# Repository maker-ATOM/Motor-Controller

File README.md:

# Motor-Controller

For firmware refer codes directory, this directory contains only PCB files

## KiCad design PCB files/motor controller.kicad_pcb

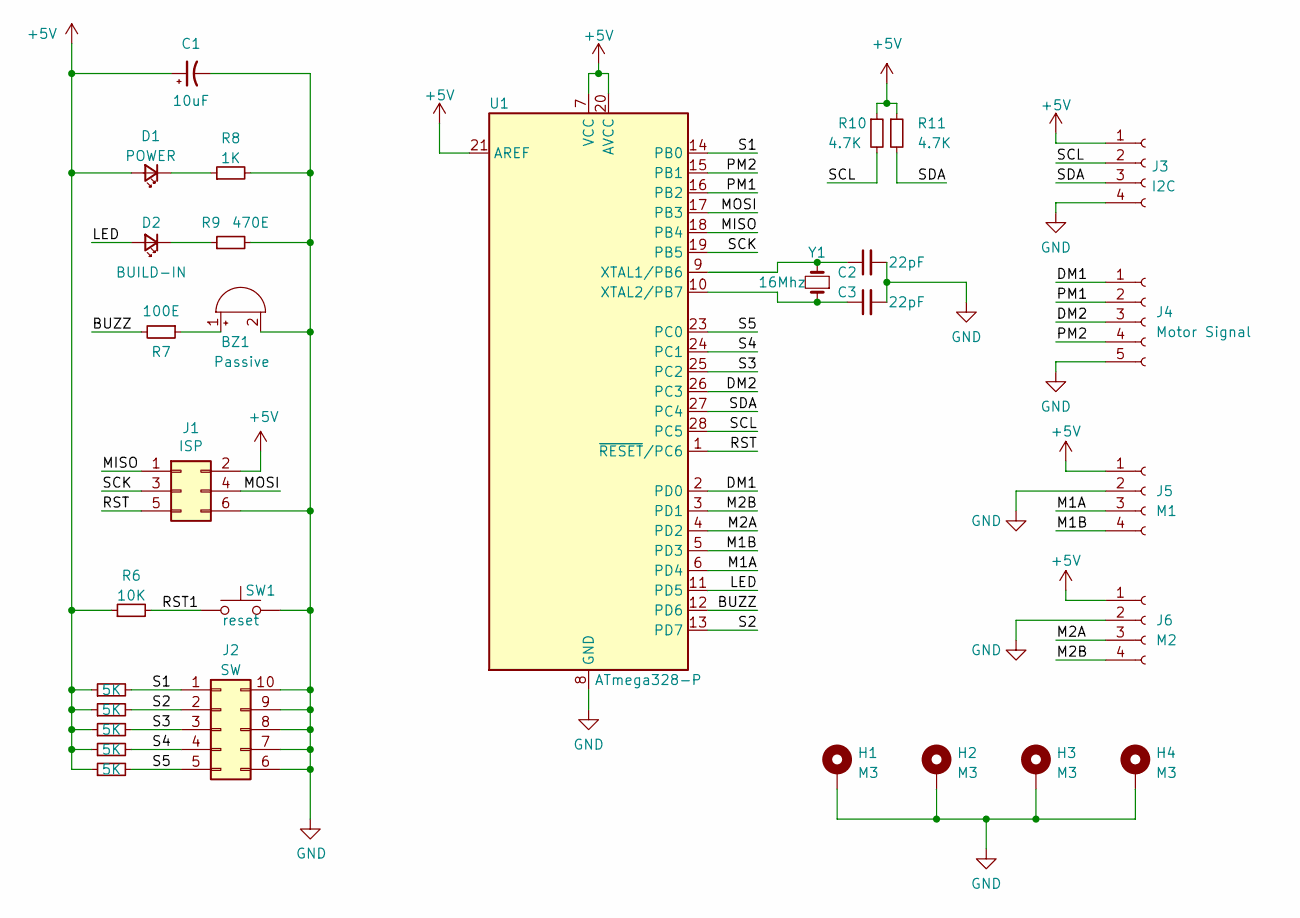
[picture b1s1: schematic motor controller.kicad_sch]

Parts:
BZ1: Passive; MagneticBuzzer_ProSignal_ABT-410-RC
C1: 10uF; CP_Elec_4x3.9
C2, C3: 22pF; C_0805_2012Metric
D1: POWER; LED_0805_2012Metric
D2: BUILD-IN; LED_0805_2012Metric
H1, H2, H3, H4: M3; MountingHole_3.2mm_M3_DIN965_Pad
J1: ISP; PinSocket_2x03_P2.54mm_Vertical
J2: SW; SW_DIP_SPSTx05_Slide_9.78x14.88mm_W7.62mm_P2.54mm
J3: I2C; JST_EH_S4B-EH_1x04_P2.50mm_Horizontal
J4: Motor Signal; PinSocket_1x05_P2.54mm_Vertical
J5: M1; JST_EH_S4B-EH_1x04_P2.50mm_Horizontal
J6: M2; JST_EH_S4B-EH_1x04_P2.50mm_Horizontal
R1, R2, R3, R4, R5: 5K; R_0805_2012Metric
R6: 10K; R_0805_2012Metric
R7: 100E; R_0805_2012Metric
R8: 1K; R_0805_2012Metric
R9: 470E; R_0805_2012Metric
R10, R11: 4.7K; R_0805_2012Metric
SW1: reset; SW_PUSH_6mm
U1: ATmega328-P; DIP-28_W7.62mm
Y1: 16Mhz; Crystal_SMD_HC49-SD

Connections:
+5V: C1.1, D1.2 (A), J1.2, J3.1, J5.1, J6.1, R1.1, R2.1, R3.1, R4.1, R5.1, R6.1, R10.1, R11.1, U1.7 (VCC), U1.20 (AVCC), U1.21 (AREF)
/BUZZ: R7.2, U1.12 (PD6)
/DM1: J4.1, U1.2 (PD0)
/DM2: J4.3, U1.26 (PC3)
/LED: D2.2 (A), U1.11 (PD5)
/M1A: J5.3, U1.6 (PD4)
/M1B: J5.4, U1.5 (PD3)
/M2A: J6.3, U1.4 (PD2)
/M2B: J6.4, U1.3 (PD1)
/MISO: J1.1, U1.18 (PB4)
/MOSI: J1.4, U1.17 (PB3)
/PM1: J4.2, U1.16 (PB2)
/PM2: J4.4, U1.15 (PB1)
/RST: J1.5, U1.1 (~RESET/PC6)
/RST1: R6.2, SW1.1
/S1: J2.1, R1.2, U1.14 (PB0)
/S2: J2.2, R2.2, U1.13 (PD7)
/S3: J2.3, R3.2, U1.25 (PC2)
/S4: J2.4, R4.2, U1.24 (PC1)
/S5: J2.5, R5.2, U1.23 (PC0)
/SCK: J1.3, U1.19 (PB5)
/SCL: J3.2, R10.2, U1.28 (PC5)
/SDA: J3.3, R11.2, U1.27 (PC4)
GND: BZ1.2 (+), C1.2, C2.2, C3.2, H1.1, H2.1, H3.1, H4.1, J1.6, J2.6, J2.7, J2.8, J2.9, J2.10, J3.4, J4.5, J5.2, J6.2, R8.2, R9.2, SW1.2, U1.8 (GND), U1.22 (GND)
unnamed: BZ1.1 (-), R7.1
unnamed: D1.1 (K), R8.1
unnamed: D2.1 (K), R9.1
unnamed: C2.1, U1.9 (XTAL1/PB6), Y1.2
unnamed: C3.1, U1.10 (XTAL2/PB7), Y1.1

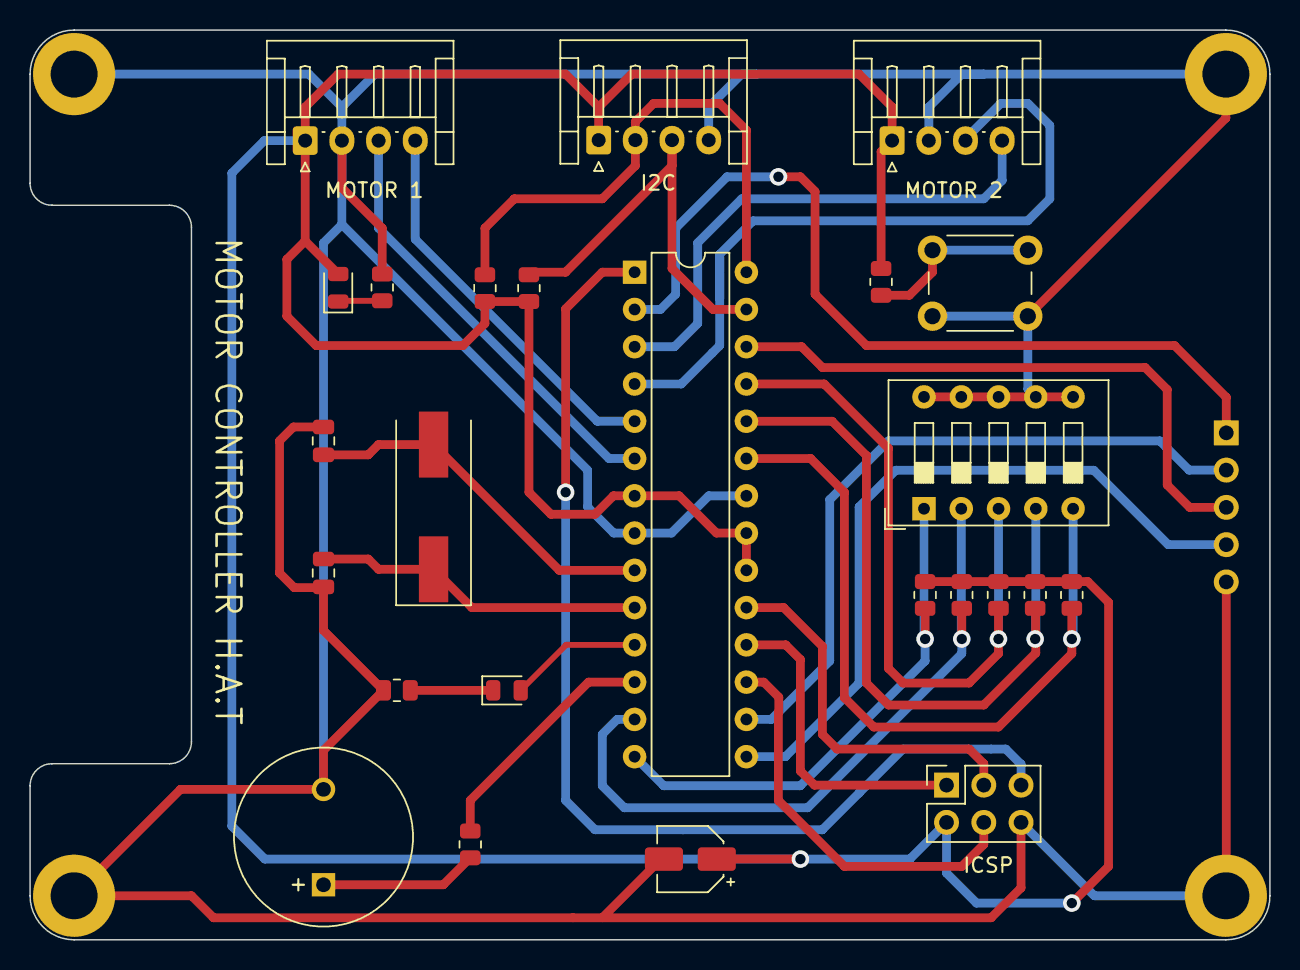
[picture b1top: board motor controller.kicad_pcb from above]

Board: 2 copper layers, 84.5 x 62.0 mm, 30 parts (1 on the bottom side), 29 nets.

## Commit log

2023-02-03 initial setup
2023-02-08 fabrication files ready
2023-02-11 generated gerber files
2023-02-14 reduced track size and genrate pdf for fabrication
2023-02-21 tested board wtih blink
2023-02-21 synced i2c code
2023-02-28 8 byte data send and recived, check for more than two byte
2023-03-04 added more jumpers
2023-03-17 added PCB backup files
2023-03-17 encoder interrupt testing
2023-03-18 patience
2023-03-21 Firmware 1.0
2023-03-23 minor changes
2023-03-23 master added
2023-04-16 improved design
2023-04-16 backups
2023-04-17 increassded power track width
2023-04-20 updated track width
2023-05-03 inc code updated
